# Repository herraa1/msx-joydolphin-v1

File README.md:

# Nintendo Gamecube controller adapter for MSX (msx-joydolphin) v1

Connect [Nintendo Gamecube controllers](https://en.wikipedia.org/wiki/GameCube_controller) to [MSX computers](https://www.msx.org/wiki/).

> [!NOTE]
> [msx-joydolphin v2](https://github.com/herraa1/msx-joydolphin-v2) is now available!

## Introduction

The msx-joydolphin is an adapter that allows connecting Nintendo Gamecube controllers to [MSX general purpose ports](https://www.msx.org/wiki/General_Purpose_port).

The main features of the msx-joydolphin v1 adapter are:
* small footprint
* made of widely available electronic components
* behaves as a cord extension between the MSX computer and the Nintendo Gamecube controller
* uses a female standard DE9 connector on the adapter's MSX joystick side
* uses a Gamecube Controller socket on the adapter's Nintendo Gamecube controller side
* no need for external power supply for wired controllers, the adapter draws current from the MSX port
* low power consumption for wired controllers (<20mA)
* serial debug provides information about the operation of the adapter
* supports WaveBird Wireless Controllers (which draw up to 150mA) when powering the adapter via USB

## Adapter Name

Why msx-joydolphin?
The first part of the name is pretty obvious: _"msx"_ as this is an adapter for MSX computers and _"joy"_ as this is a joystick adapter.
The _"dolphin"_ part comes from the project codename assigned to the Nintendo Gamecube during its development.

## [Hardware](hardware/kicad/)

The msx-joydolphin v1 adapter uses an [Arduino Nano](https://store.arduino.cc/products/arduino-nano) to convert the [Nintendo Gamecube controller signalling](http://www.int03.co.uk/crema/hardware/gamecube/gc-control.html) to the [MSX joystick standard signalling](https://www.msx.org/wiki/Joystick_control).

A small printed circuit board (PCB) is used to easily bind all components:
* The Arduino Nano is connected using female headers
* PH2.0 connectors are used to connect cable extensions
* A 2.54 pitch debug header is added for convenience
* Through-hole components are used on the front side
* Surface mount device (SMD) components are used on the back side
  * The SMD components use footprints optimized for hand-soldering

Connection to the MSX general purpose port is implemented using a DE9 joystick extension cable with a female DE9 connector on one side and a loose end on the other side.
The MSX joystick extension cable loose end is wired according to the following pinout mapping.

|  |
|:--|
| MSX joystick connector pinout, from controller plug side |

| MSX side pin | Cable color (may vary) | Signal | Arduino Nano side (port/pin/number) |
| ------------ | ---------------------- | ------ | ----------------------------------- |
| 5            | Brown                  | +5v    | _/5V/27                             |
| 4            | Orange                 | RIGHT  | PB3/D11/14                          |
| 3            | Grey                   | LEFT   | PB2/D10/13                          |
| 2            | Black                  | DOWN   | PB1/D9/12                           |
| 1            | Red                    | UP     | PB0/D8/11                           |
| 6            | Green                  | TRIGA  | PB4/D12/15                          |
| 7            | White                  | TRIGB  | PB5/D13/16                          |
| 8            | Blue                   | OUT    | PD2/D2/5                            |
| 9            | Yellow                 | GND    | _/GND/4,29                          |

The msx-joydolphin-v1 adapter ignores the MSX general purpose pin8 (OUT) signal. This is not a problem in general, but can cause incompatibilities with specific software, like MSX-HID [^2], which uses pin8 to try to guess which
kind of device is connected to a MSX general purpose I/O port. For MSX-HID, holding the Trigger B button, will put the software in FM-Towns compatible mode which will make the adapter functional.

The adapter uses open collector outputs (putting the related Arduino Nano pins in INPUT mode with pull-up registers active when in logic "1" and in OUTPUT mode LOW when in logic "0") which makes the adapter safer [^3] than the
standard MSX joystick schematic depicted in the MSX Technical Data Book, as it avoids a series of undesired conditions that can lead to bus contention/short circuits.

Power is drawn from the +5V signal of the MSX general purpose port, which is capable of delivering up to 50mA [^1].
The msx-joydolphin v1 draws below 20mA from the port when a wired controller is connected, so it is on the safe side. Anyway, the msx-joydolphin adapter uses a Positive Temperature Coeficient (PTC) resettable fuse of 50mA (F1) to limit current in case something goes wrong.

Also on the power side, a [1N5817 Schottky diode](https://www.onsemi.com/download/data-sheet/pdf/1n5817-d.pdf) (D1) is used to avoid leaking current from the msx-joydolphin adapter to the MSX in case the USB port of the Arduino Nano is connected to a computer or power supply while the adapter is plugged into an MSX.

Connection to the Nintendo Gamecube controller is done via a Nintendo Gamecube controller extension cable with a controller socket on one side and a loose end on the other side.
The Nintendo Gamecube controller extension cable loose end is wired according to the following pinout mapping.

|  |
|:--|
| Nintendo Gamecube connector pinout, from Nintendo Gamecube side |

| Gamecube socket pin | Cable color official | Cable color actual (may vary) | Signal | Comment                                                                   | Arduino Nano side (port/pin/number) |
| ------------------- | ---------------------| ----------------------------- | ------ | ------------------------------------------------------------------------- | ----------------------------------- |
| 1                   | Yellow               | White                         | +5v    | rumble, not used                                                          | N/C                                 |
| 2                   | Red                  | Red                           | DAT    | data line, uses 3v3 logic so it connects via a level shifter to PD7/D7/10 | \*( PD7/D7/10 )                     |
| 3                   | Green                | Black                         | GND    | ground                                                                    | _/GND/4,29                          |
| 4                   | White                | Blue                          | GND    | ground                                                                    | _/GND/4,29                          |
| 5                   |                      |                               |        |                                                                           | N/C                                 |
| 6                   | Blue                 | Green                         | 3.43v  | power line, 3v3                                                           | _/3v3/17                            |
| 7                   | Black                | N/A                           | GND    | ground                                                                    | N/C                                 |

The Nintendo Gamecube controller uses 3.3V for power and logic, except for the rumble motor which uses 5V.

Power for the Nintendo Gamecube controller is provided by the 3.3V pin of the FT232RL integrated in the Arduino Nano, which is capable of delivering up to 50mA [^2], enough to power a wired game controller.

As the Arduino Nano is a 5V logic microcontroller, the msx-joydolphin adapter uses a voltage level shifter based on the [BSS138 N-Channel Logic Level Enhancement Mode Field Effect Transistor](https://www.onsemi.com/pdf/datasheet/bss138-d.pdf) (Q1) to convert the Nintendo Gamecube controller DAT signal between 3.3V and 5V logic levels.

> [!WARNING]
> Do NOT connect the DAT line of the Nintendo Gamecube controller to the Arduino Nano directly, always use a voltage level shifter.
> The game controller may get damaged if you connect a 5V signal directly to the 3.3V DAT line.

If a WaveBird Wireless Controller is connected then the msx-joydolphin adapter needs to be powered via the mini USB port of the Arduino Nano, as the power consumption (150mA) is higher than what the MSX joystick port can deliver.
Althought it won't work, it is safe to connect a WaveBird Wireless Controller dongle without connecting an external USB power supply thanks to the current limitation of the PTC.
Also, connection of an external USB power supply to the Arduino Nano won't back-power the MSX computer thanks to the Schottky diode reverse current protection.

## [Firmware](firmware/msx-joydolphin-v1/)

The msx-joydolphin v1 adapter firmware uses [NicoHood's Nintendo library](https://github.com/NicoHood/Nintendo) to read the Nintendo Gamecube controller status, and it is heavily inspired on [Daniel Jose Viana "Danjovic" firmware](https://github.com/Danjovic/MSX/blob/master/NSX-64) for a similar adapter for Nintendo 64 joysticks.

The following elements are used as inputs:
* digital pad (D-Pad), as direction arrows
* analog pad, as direction arrows
* A button, as Trigger 1
* B button, as Trigger 2

Those elements' status are processed by the msx-joydolphin firmware and transformed into MSX general purpose port's signals on the fly.

The firmware uses Arduino Nano's sleep capabilities to reduce power consumption when a wired controller is used.

## [Enclosure](enclosure/)

### Acrylic

A simple acrylic enclosure design for the project is provided to protect the electronics components and provide strain relief for the extension cords.

The enclosure uses a 3mm acrylic sheet.

Later designs of the enclosure allow access to the USB port of the Arduino Nano without having to open it.

### Plastic

Another enclosure option is using an off-the-shelf plastic case of 60x36x17mm.

When using this option, the Arduino Nano must be soldered directly to the msx-joydolphin v1 board and its pin header legs must be trimmed down in order to fit within the reduced space of the case.

## References

MSX General Purpose port
* https://www.msx.org/wiki/General_Purpose_port

Gamecube controller pinout
* https://allpinouts.org/pinouts/connectors/videogame/nintendo-gamecube-controller-connector-pinout/
* http://www.int03.co.uk/crema/hardware/gamecube/gc-control.html

Arduino Nano pinout
* https://content.arduino.cc/assets/Pinout-NANO_latest.pdf
* https://www.makerguides.com/arduino-nano/

Nico Hood Nintendo Gamecube Joystick arduino library
* https://github.com/NicoHood/Nintendo

Daniel Jose Viana "Danjovic" NSX-64 project
* https://github.com/Danjovic/MSX/blob/master/NSX-64

Gamecube controller IDs
* https://www.gc-forever.com/yagcd/chap9.html#sec9

[^1]: https://www.msx.org/wiki/General_Purpose_port
[^2]: https://www.mouser.es/datasheet/2/163/DS_FT232R-11534.pdf
[^3]: https://www.msx.org/wiki/Joystick/joypad_controller (see "Undesired Conditions")

## Image Sources

* https://www.oshwa.org/open-source-hardware-logo/
* https://consolemods.org/wiki/images/a/a1/GameCube_Controller_Pinout.svg
* https://en.wikipedia.org/wiki/File:Numbered_DE9_Diagram.svg
* https://commons.wikimedia.org/wiki/File:Video_Game_Controller_(56427)_-_The_Noun_Project.svg
* https://logo-timeline.fandom.com/wiki/GameCube?file=Nintendo_Dolphin_1999.svg

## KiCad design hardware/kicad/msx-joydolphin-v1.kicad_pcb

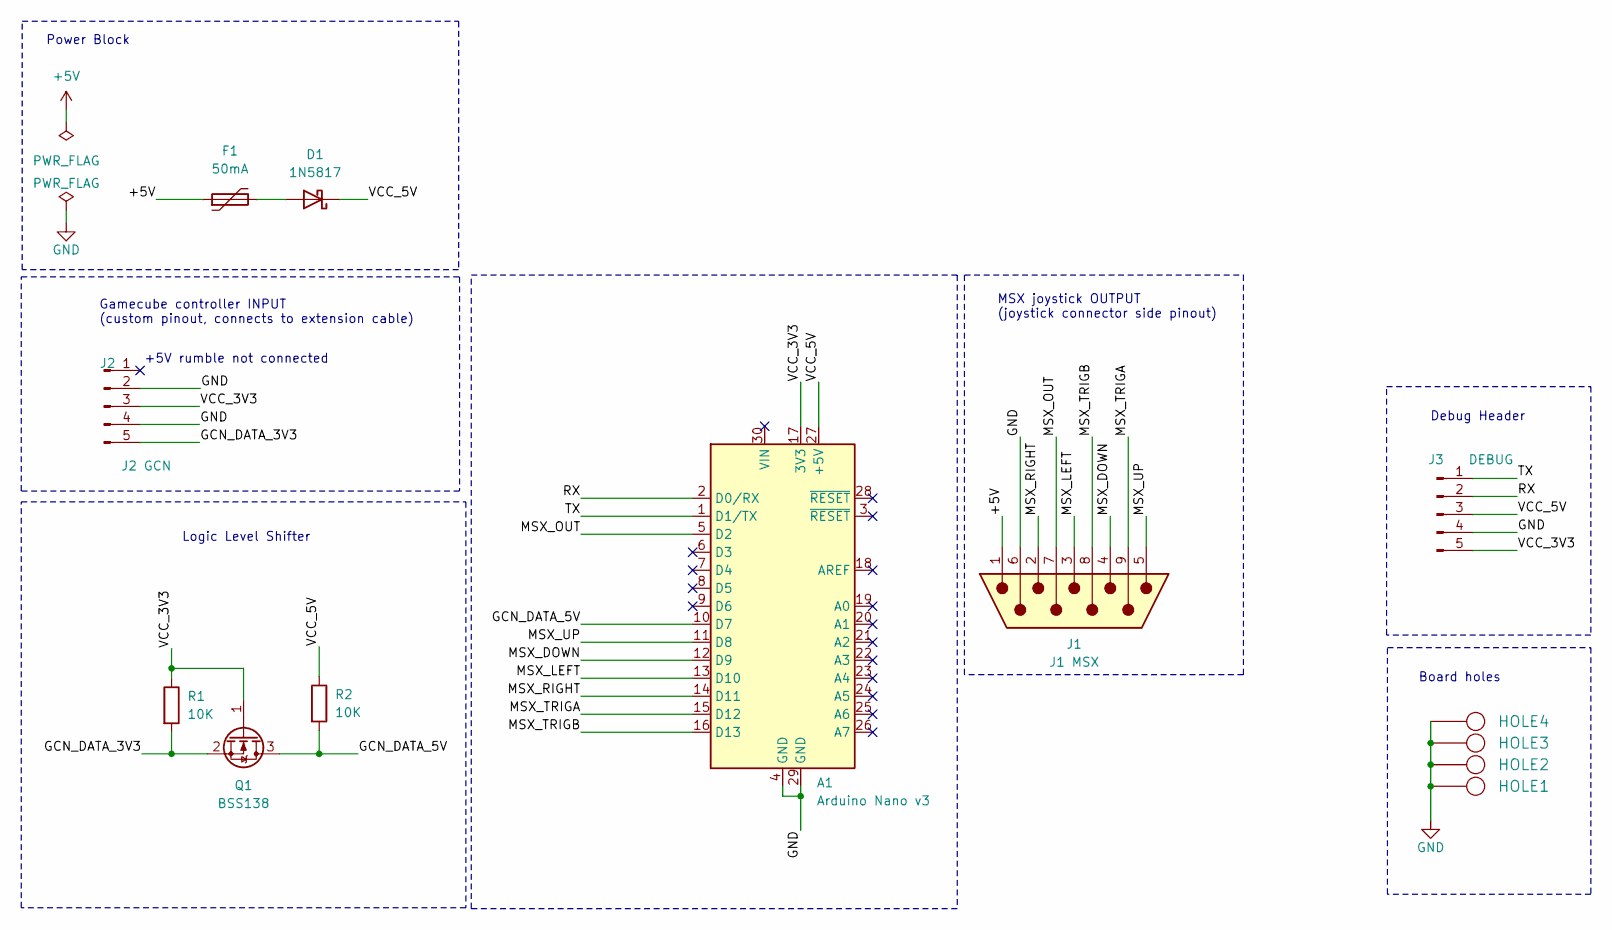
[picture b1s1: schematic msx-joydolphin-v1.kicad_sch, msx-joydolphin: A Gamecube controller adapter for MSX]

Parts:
A1: Arduino Nano v3; Arduino_Nano
D1: 1N5817; D_DO-41_SOD81_P10.16mm_Horizontal
F1: 50mA; C_Disc_D7.5mm_W2.5mm_P5.00mm
HOLE1, HOLE2, HOLE3, HOLE4: HOLE; Hole_3mm
J1: J1 MSX; JST_PH_B9B-PH-K_1x09_P2.00mm_Vertical
J2: J2 GCN; JST_PH_B5B-PH-K_1x05_P2.00mm_Vertical
J3: DEBUG; Conn_Pin_Header_5x1_2.54mm
Q1: BSS138; SOT-23
R1, R2: 10K; R_1206_3216Metric_Pad1.30x1.75mm_HandSolder

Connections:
+5V: F1.1, J1.1
/GCN_DATA_3V3: J2.5, Q1.2 (S), R1.2
/GCN_DATA_5V: A1.10 (D7), Q1.3 (D), R2.2
/MSX_DOWN: A1.12 (D9), J1.4
/MSX_LEFT: A1.13 (D10), J1.3
/MSX_OUT: A1.5 (D2), J1.7
/MSX_RIGHT: A1.14 (D11), J1.2
/MSX_TRIGA: A1.15 (D12), J1.9
/MSX_TRIGB: A1.16 (D13), J1.8
/MSX_UP: A1.11 (D8), J1.5
/RX: A1.2 (D0/RX), J3.2
/TX: A1.1 (D1/TX), J3.1
/VCC_3V3: A1.17 (3V3), J2.3, J3.5, Q1.1 (G), R1.1
/VCC_5V: A1.27 (+5V), D1.1 (K), J3.3, R2.1
GND: A1.4 (GND), A1.29 (GND), HOLE1.1, HOLE2.1, HOLE3.1, HOLE4.1, J1.6, J2.2, J2.4, J3.4
unnamed: D1.2 (A), F1.2

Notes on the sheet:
MSX joystick OUTPUT (joystick connector side pinout)
Debug Header
+5V rumble not connected
Board holes
Power Block
Logic Level Shifter
Gamecube controller INPUT (custom pinout, connects to extension cable)

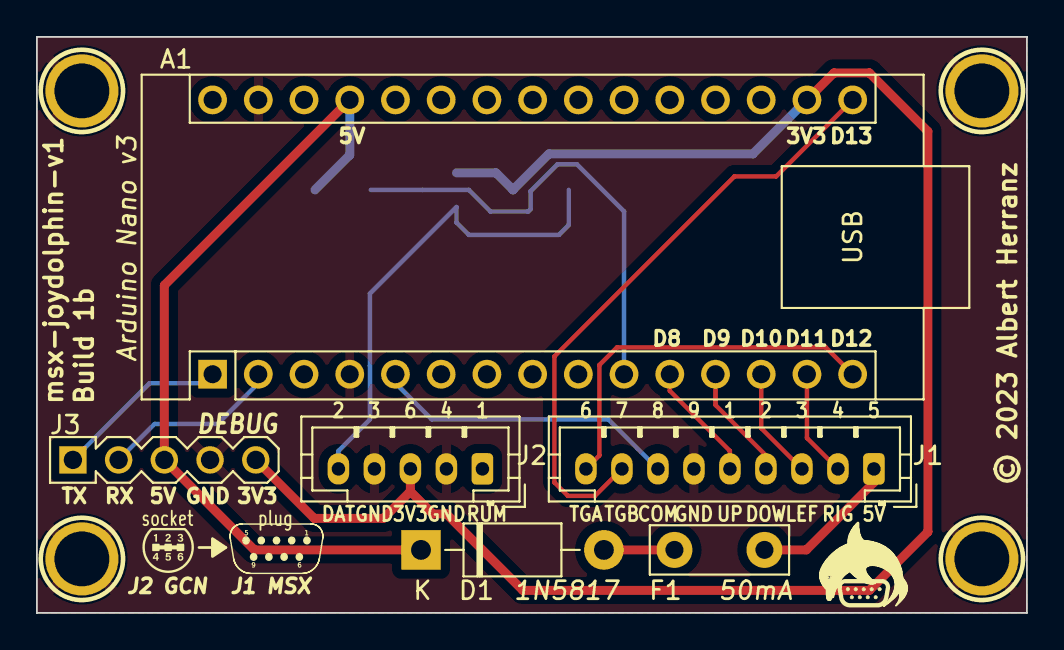
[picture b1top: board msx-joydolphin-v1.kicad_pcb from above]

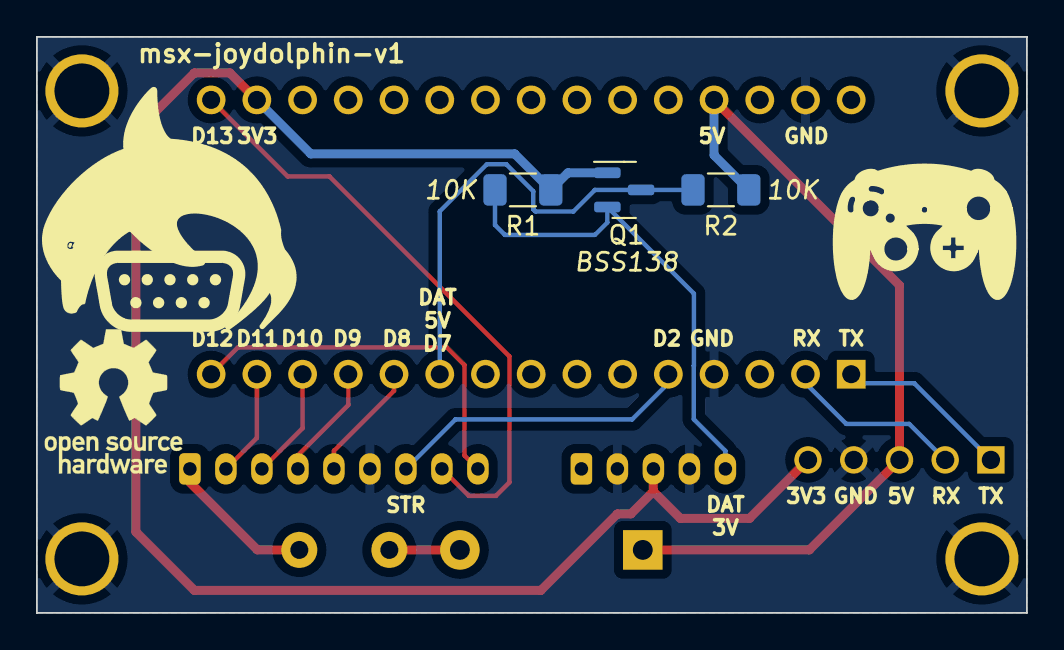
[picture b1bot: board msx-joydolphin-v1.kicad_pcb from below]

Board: 2 copper layers, 55.0 x 32.0 mm, 13 parts (3 on the bottom side), 16 nets.

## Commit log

2023-10-03 Initial commit.
2023-10-03 Enrich some comments, point main links to enclosing dirs
2023-10-21 Rename joystick signals, add PORT_ prefix
2023-10-21 Disable debugging
2023-10-21 Firmware improvements.
    - We can't use the builtin led as we use the pin for TRIG2,
    so now we use the TX led for reporting status
    - Wavebirds require at least 150mA which cannot be provided
    through the MSX joystick port. Now wavebirds work if
    the joydolphin is powered via the Nano usb port
    - Sleeping is now only enabled for wired controllers, as
2023-10-21 Untested enclosure modification to allow USB port usage
2023-10-21 Update README with new features
2023-10-21 Reword feature to use homogeneous phrasing
2023-10-22 ignore librecad backup files
2023-10-22 enclosure: slightly move strain relief hole for msx extension, and regroup pieces
2023-10-22 firmware: fix indentation error
2023-11-01 hardware: miscelanoues enhancements
    - Add top copper fill area for ground
    Save some chemicals when etching the top layer, and possibly enhance signal
    integrity.
    - Change board width
    Reduce board width from 56mm to 55mm to allow using alterante off-the-shelf
    plastic case.
2023-11-13 Fix spurious trigger 2 press on startup
    We are unfortunately using pin 13 of Arduino Nano for controlling trigger 2.
    That pin is hardwired to the builtin led which causes it to lit (slightly) when
    trigger 2 is not pressed and thus pulled high by the MSX side.
    It also causes a spurious press on startup.
    Instead of configuring the pin as input (high impedance) when trigger 2
    is not pressed, configure the pin as output and set it to high. When
2023-11-14 Update readme to reflect new led behavior
2024-02-01 firmware: fixes unsafe TRG2 handling and aligns to standard joystick MSX behaviour on initial board revision
2024-02-01 readme: ignore arduino nano led
2024-02-01 readme: added information about acrylic and plastic cases
2024-02-05 firmware: pass HIDtest v3.2
2024-02-10 firmware: improve pin8 tracking
2024-02-17 firmware: revert to ignore pin8
    Due to the strict timings required to read the gamecube controller
    interrupts are disabled during those periods which lead to
    losing interrupts related to pin8 changes.
    Although the previous code passed the HIDtest test, observing
    the signals with a osciloscope reveals that some times pin8 is
    not honored correctly because of the lost pin8 change interrupts.
2024-02-21 readme: clarify behavior
2024-02-21 readme: add missing foot note
2024-02-21 firmware: unify condition after last cleanup
2024-02-21 board: use OUT,TRGA,TRGB instead of STR,TRG1,TRG2
2024-04-20 link to msx-joydolphin v2

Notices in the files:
hardware/kicad/msx-joydolphin-v1.kicad_pcb:
© 2023 Albert Herranz
